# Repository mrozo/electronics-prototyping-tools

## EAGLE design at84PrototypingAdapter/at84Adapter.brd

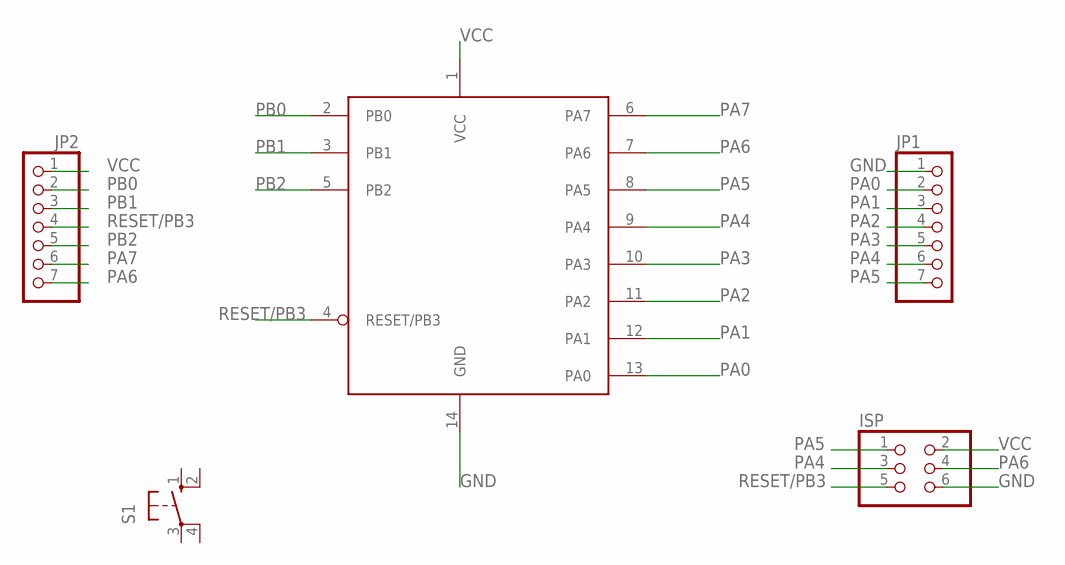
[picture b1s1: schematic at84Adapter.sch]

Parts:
ISP: PINHD-2X3; 2X03
JP1, JP2: PINHD-1X7; 1X07
S1: 10-XX; B3F-10XX
U1: AT84; DIL14

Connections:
GND: ISP.6, JP1.1, U1.14 (GND)
PA0: JP1.2, U1.13 (PA0)
PA1: JP1.3, U1.12 (PA1)
PA2: JP1.4, U1.11 (PA2)
PA3: JP1.5, U1.10 (PA3)
PA4: ISP.3, JP1.6, U1.9 (PA4)
PA5: ISP.1, JP1.7, U1.8 (PA5)
PA6: ISP.4, JP2.7, U1.7 (PA6)
PA7: JP2.6, U1.6 (PA7)
PB0: JP2.2, U1.2 (PB0)
PB1: JP2.3, U1.3 (PB1)
PB2: JP2.5, U1.5 (PB2)
RESET/PB3: ISP.5, JP2.4, U1.4 (RESET/PB3)
VCC: ISP.2, JP2.1, U1.1 (VCC)

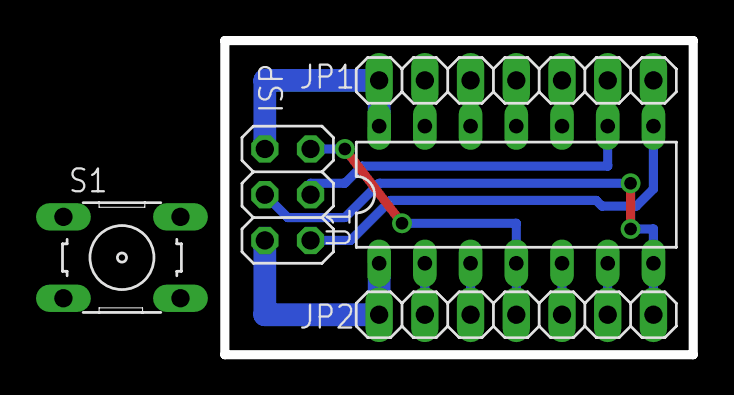
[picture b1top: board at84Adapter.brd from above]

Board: 2 copper layers, 26.0 x 17.5 mm, 5 parts (0 on the bottom side), 14 nets.

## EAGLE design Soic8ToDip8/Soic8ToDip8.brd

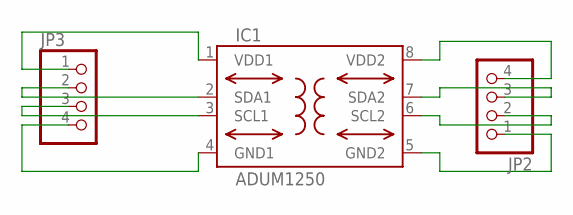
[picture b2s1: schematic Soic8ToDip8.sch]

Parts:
IC1: ADUM1250; SO8-COOL
JP2, JP3: PINHD-1X4; 1X04

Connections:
GND1: IC1.4 (GND1), JP3.4
GND2: IC1.5 (GND2), JP2.1
unnamed: IC1.3 (SCL1), JP3.3
unnamed: IC1.2 (SDA1), JP3.2
unnamed: IC1.7 (SDA2), JP2.3
unnamed: IC1.6 (SCL2), JP2.2
VDD1: IC1.1 (VDD1), JP3.1
VDD2: IC1.8 (VDD2), JP2.4

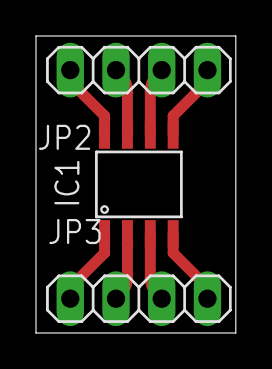
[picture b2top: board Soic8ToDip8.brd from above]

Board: 2 copper layers, 11.1 x 16.5 mm, 3 parts (0 on the bottom side), 8 nets.

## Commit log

2015-10-16 Creation of soic8 to dip8 adapter and raspberry pi display gpio fix board
2015-10-20 added Atmel ATiny84 minimal development board
